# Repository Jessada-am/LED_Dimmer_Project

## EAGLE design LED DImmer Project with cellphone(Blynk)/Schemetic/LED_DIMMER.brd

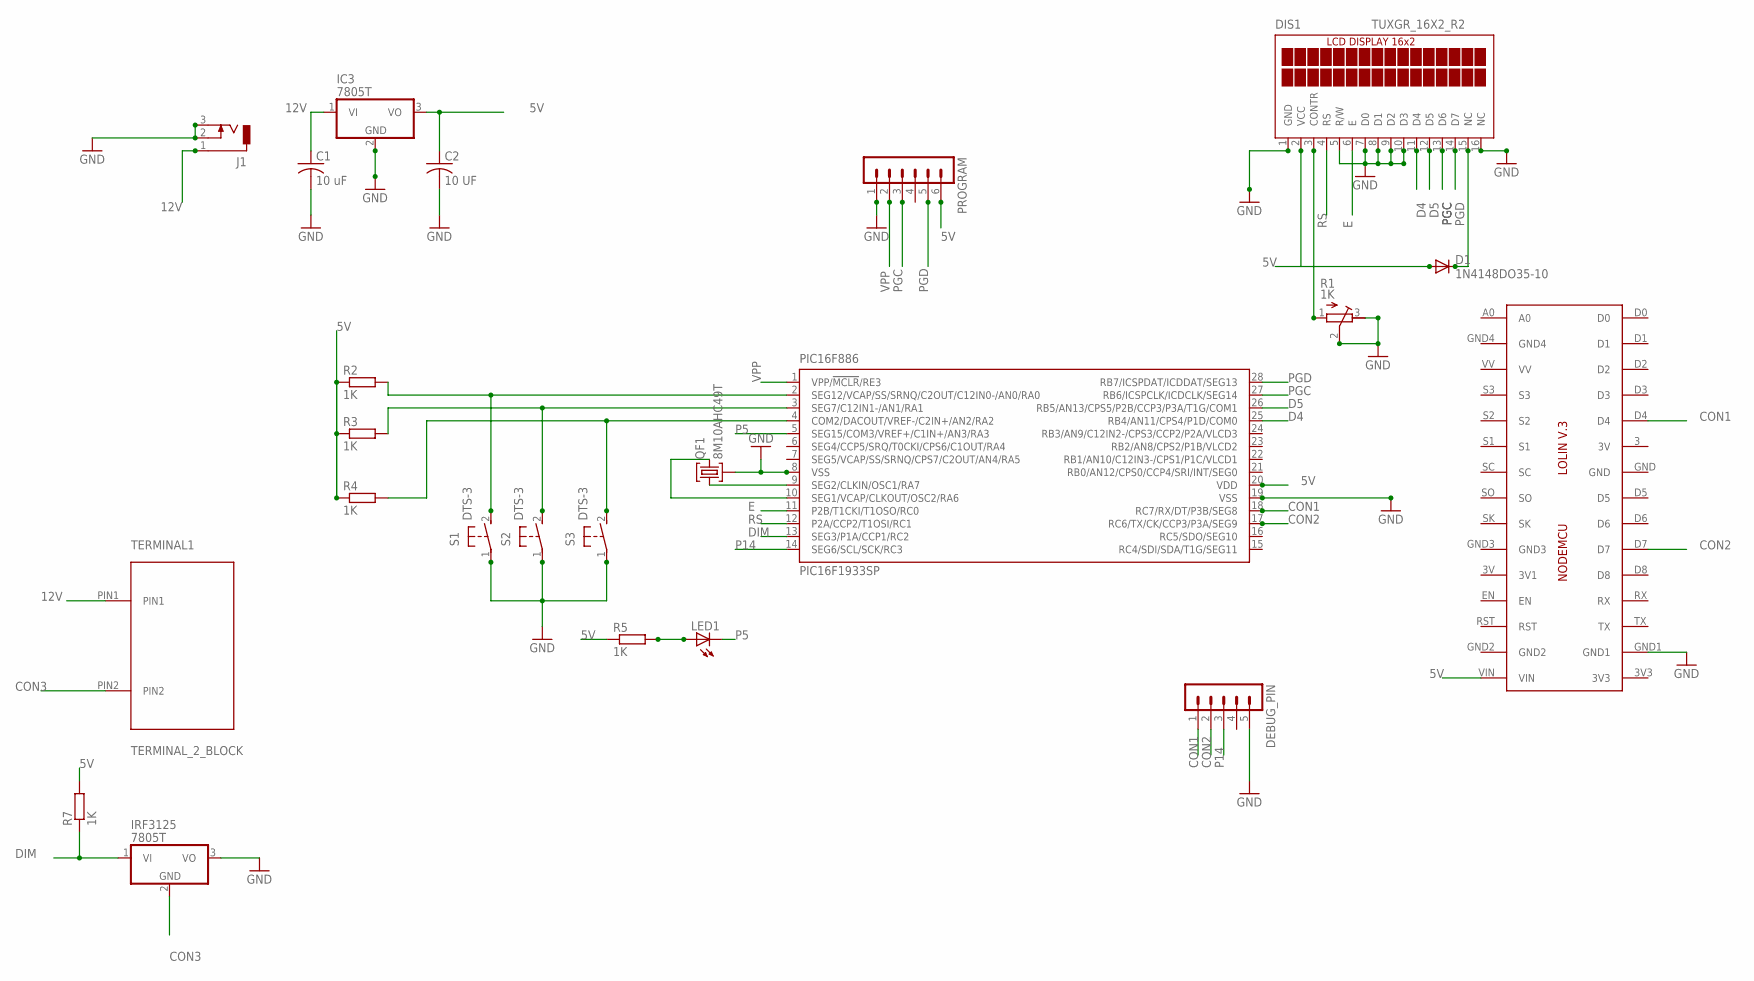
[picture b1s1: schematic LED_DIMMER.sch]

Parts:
C1: 10 uF; C025-025X050
C2: 10 UF; C025-025X050
D1: 1N4148DO35-10; DO35-10
DEBUG_PIN: MA05-1
DIS1: TUXGR_16X2_R2
IC2: LOLINV3
IC3: 7805T; TO220H
IRF3125: 7805T; TO220H
J1: DCJ0303
LED1: LED_ELD260; LED_LD260
PIC16F886: PIC16F1933SP; DIL28-3
PROGRAM: MA06-1
QF1: 8M10AHC49T; HC49U
R1: 1K; RTRIM64W
R2, R3, R4, R5, R7: 1K; 0204/7
S1, S2, S3: DTS-3
TERMINAL1: TERMINAL_2_BLOCK

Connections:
5V: C2.1, D1.A, DIS1.2 (VCC), IC2.VIN, IC3.3 (VO), PIC16F886.20 (VDD), PROGRAM.6, R2.1, R3.1, R4.1, R5.1, R7.2
12V: C1.1, IC3.1 (VI), J1.1, TERMINAL1.PIN1
CON1: DEBUG_PIN.1, IC2.D4, PIC16F886.18 (RC7/RX/DT/P3B/SEG8)
CON2: DEBUG_PIN.2, IC2.D7, PIC16F886.17 (RC6/TX/CK/CCP3/P3A/SEG9)
CON3: IRF3125.2 (GND), TERMINAL1.PIN2
D4: DIS1.11 (D4), PIC16F886.25 (RB4/AN11/CPS4/P1D/COM0)
D5: DIS1.12 (D5), PIC16F886.26 (RB5/AN13/CPS5/P2B/CCP3/P3A/T1G/COM1)
DIM: IRF3125.1 (VI), PIC16F886.13 (SEG3/P1A/CCP1/RC2), R7.1
E: DIS1.6 (E), PIC16F886.11 (P2B/T1CKI/T1OSO/RC0)
GND: C1.2, C2.2, DEBUG_PIN.5, DIS1.1 (GND), DIS1.5 (R/W), DIS1.7 (D0), DIS1.8 (D1), DIS1.9 (D2), DIS1.10 (D3), DIS1.16 (NC), IC2.GND1, IC3.2 (GND), IRF3125.3 (VO), J1.2, J1.3, PIC16F886.8 (VSS), PIC16F886.19 (VSS), PROGRAM.1, QF1.2, R1.2 (S), R1.3 (E), S1.1, S2.1, S3.1
unnamed: PIC16F886.2 (SEG12/VCAP/SS/SRNQ/C2OUT/C12IN0-/AN0/RA0), R2.2, S1.2
unnamed: PIC16F886.9 (SEG2/CLKIN/OSC1/RA7), QF1.1
unnamed: PIC16F886.10 (SEG1/VCAP/CLKOUT/OSC2/RA6), QF1.3
unnamed: PIC16F886.3 (SEG7/C12IN1-/AN1/RA1), R3.2, S2.2
unnamed: PIC16F886.4 (COM2/DACOUT/VREF-/C2IN+/AN2/RA2), R4.2, S3.2
unnamed: D1.C, DIS1.15 (NC)
unnamed: DIS1.3 (CONTR), R1.1 (A)
unnamed: LED1.A, R5.2
P5: LED1.K (C), PIC16F886.5 (SEG15/COM3/VREF+/C1IN+/AN3/RA3)
P14: DEBUG_PIN.3, PIC16F886.14 (SEG6/SCL/SCK/RC3)
PGC: DIS1.13 (D6), PIC16F886.27 (RB6/ICSPCLK/ICDCLK/SEG14), PROGRAM.3
PGD: DIS1.14 (D7), PIC16F886.28 (RB7/ICSPDAT/ICDDAT/SEG13), PROGRAM.5
RS: DIS1.4 (RS), PIC16F886.12 (P2A/CCP2/T1OSI/RC1)
VPP: PIC16F886.1 (VPP/!MCLR!/RE3), PROGRAM.2

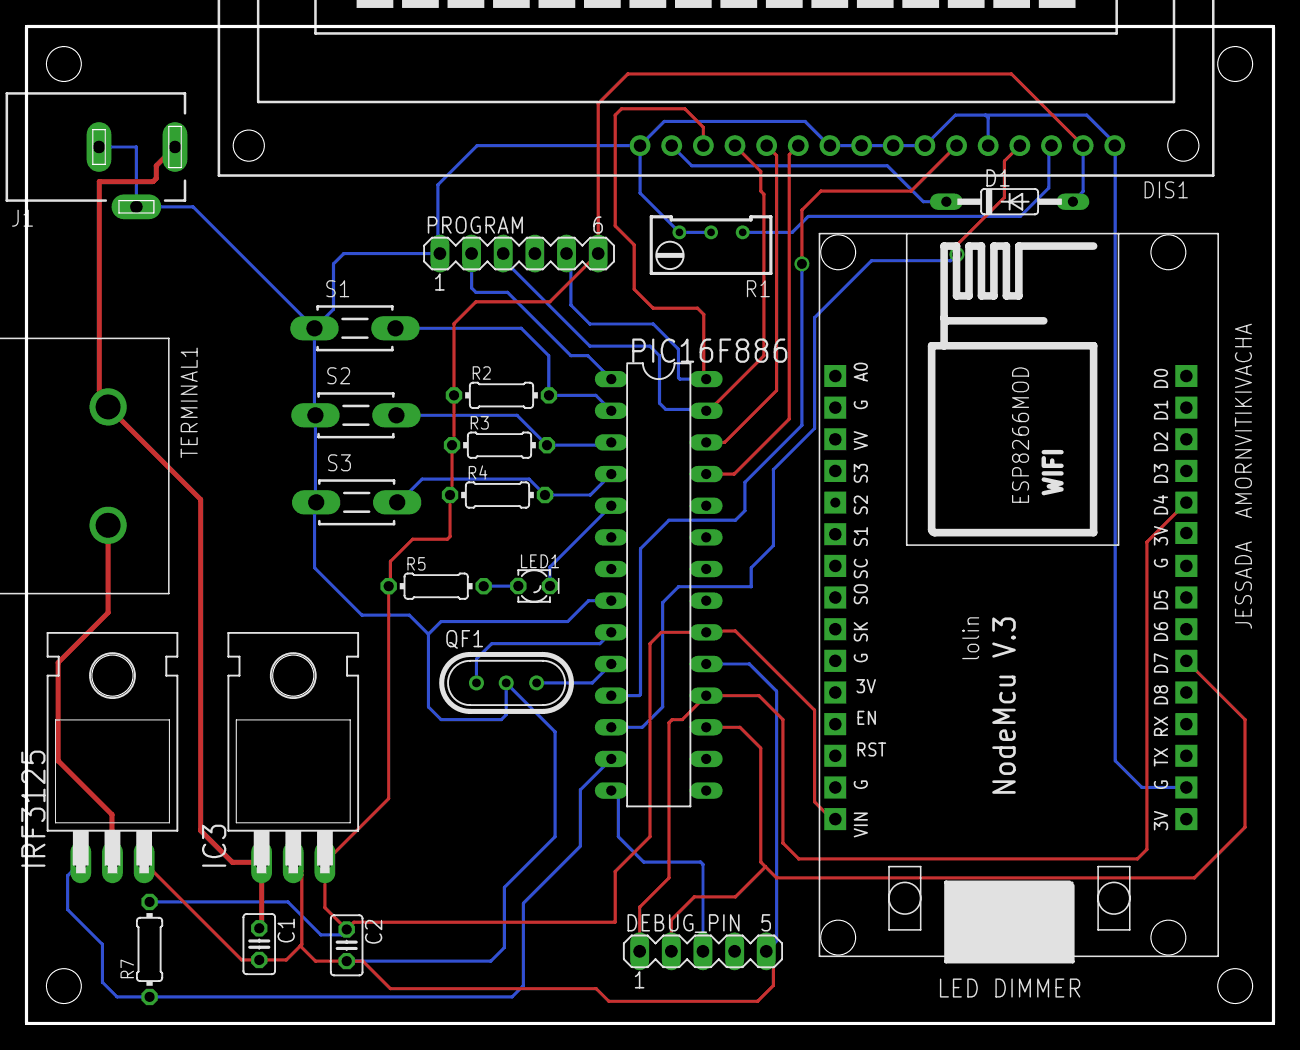
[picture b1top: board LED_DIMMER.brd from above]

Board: 2 copper layers, 100.1 x 80.0 mm, 23 parts (0 on the bottom side), 24 nets.
